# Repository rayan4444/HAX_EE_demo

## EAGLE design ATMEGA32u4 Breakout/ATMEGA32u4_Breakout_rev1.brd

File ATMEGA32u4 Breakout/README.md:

# ATMEGA32u4 Breakout v1

The ATEGA32u4 is the main microcontroller on the Arduino Leonardo and Micro. Its main advantage over the standard ATMEGA328P chip from the UNO lies in its native USB support, which makes it very easy to communicate with from a PC or SBC. This module breaks out most of the ATMEGA32u4 peripherals and is meant to be used in a Distributed Control System architecture.

## Ordering the PCB
Gerber files, Drill files and BOM for this board are provided in this repo.
If you don't know how to order PCBs, check out the HAX Wiki: [making a PCB (prototyping)](https://wiki.hax.co/Making_a_PCB_(prototyping)#Ordering_the_Board)

## Features
* Native USB
* RS-485 bus
* I2C breakout x 2
* SPI breakout x 1
* Analog pins breakout x 5 (ADC)
* PWM pins breakout x 4
* Programmable LED (on digital pin 13)
* Digital I/O breakout x 4 with optional MOSFETs:
  * solder a 0 ohm resistor where designated to use standard digital output
  * solder N-MOSFET circuitry to use it to toggle higher voltage outputs
* Optional High voltage input (for the N-MOSFET outputs)

## Programming Instructions
* The native USB port cannot be used immediately after assembling the PCB. You need to burn the Arduino Leonardo or Micro bootloader on the MCU first.
* You can use another Arduino and the SPI breakout 3x2 header to burn the bootloader ([tutorial](https://www.arduino.cc/en/tutorial/arduinoISP))
> Tip: If you have issues burning the bootloader, try connecting the receiver's (aka the new PCB) RST line to pin 10 of the programmer Arduino (aka Arduino you are using to burn the bootloader). On some boards the ICSP header's RST is not connected to pin 10 by default.

* After burning the bootloader, you can connect your ATMEGA32u4 breakout to your PCB/SBC with standard Micro USB cable and use the Arduino IDE to flash it.

## Examples
* *Short description of code in "examples" folder*
* *Link description/projects/photos where people have used this*

## Datasheets
* MCU: [ATMEGA32u4](http://ww1.microchip.com/downloads/en/devicedoc/atmel-7766-8-bit-avr-atmega16u4-32u4_datasheet.pdf)
* RS-485 transceiver: [MAX485](https://datasheets.maximintegrated.com/en/ds/MAX1487-MAX491.pdf)
* MOSFET: [IRLHM630TRPBF](https://www.infineon.com/dgdl/irlhm630pbf.pdf?fileId=5546d462533600a401535663951725a5)

## References
* [RS-485 basics](https://learn.sparkfun.com/tutorials/ast-can485-hookup-guide/introduction-to-rs485)
* Writing a custom RS485 protocol (*add link*)

## Feedback and Questions
Feel free to open an issue to report bugs, ask questions, suggest features, etc.

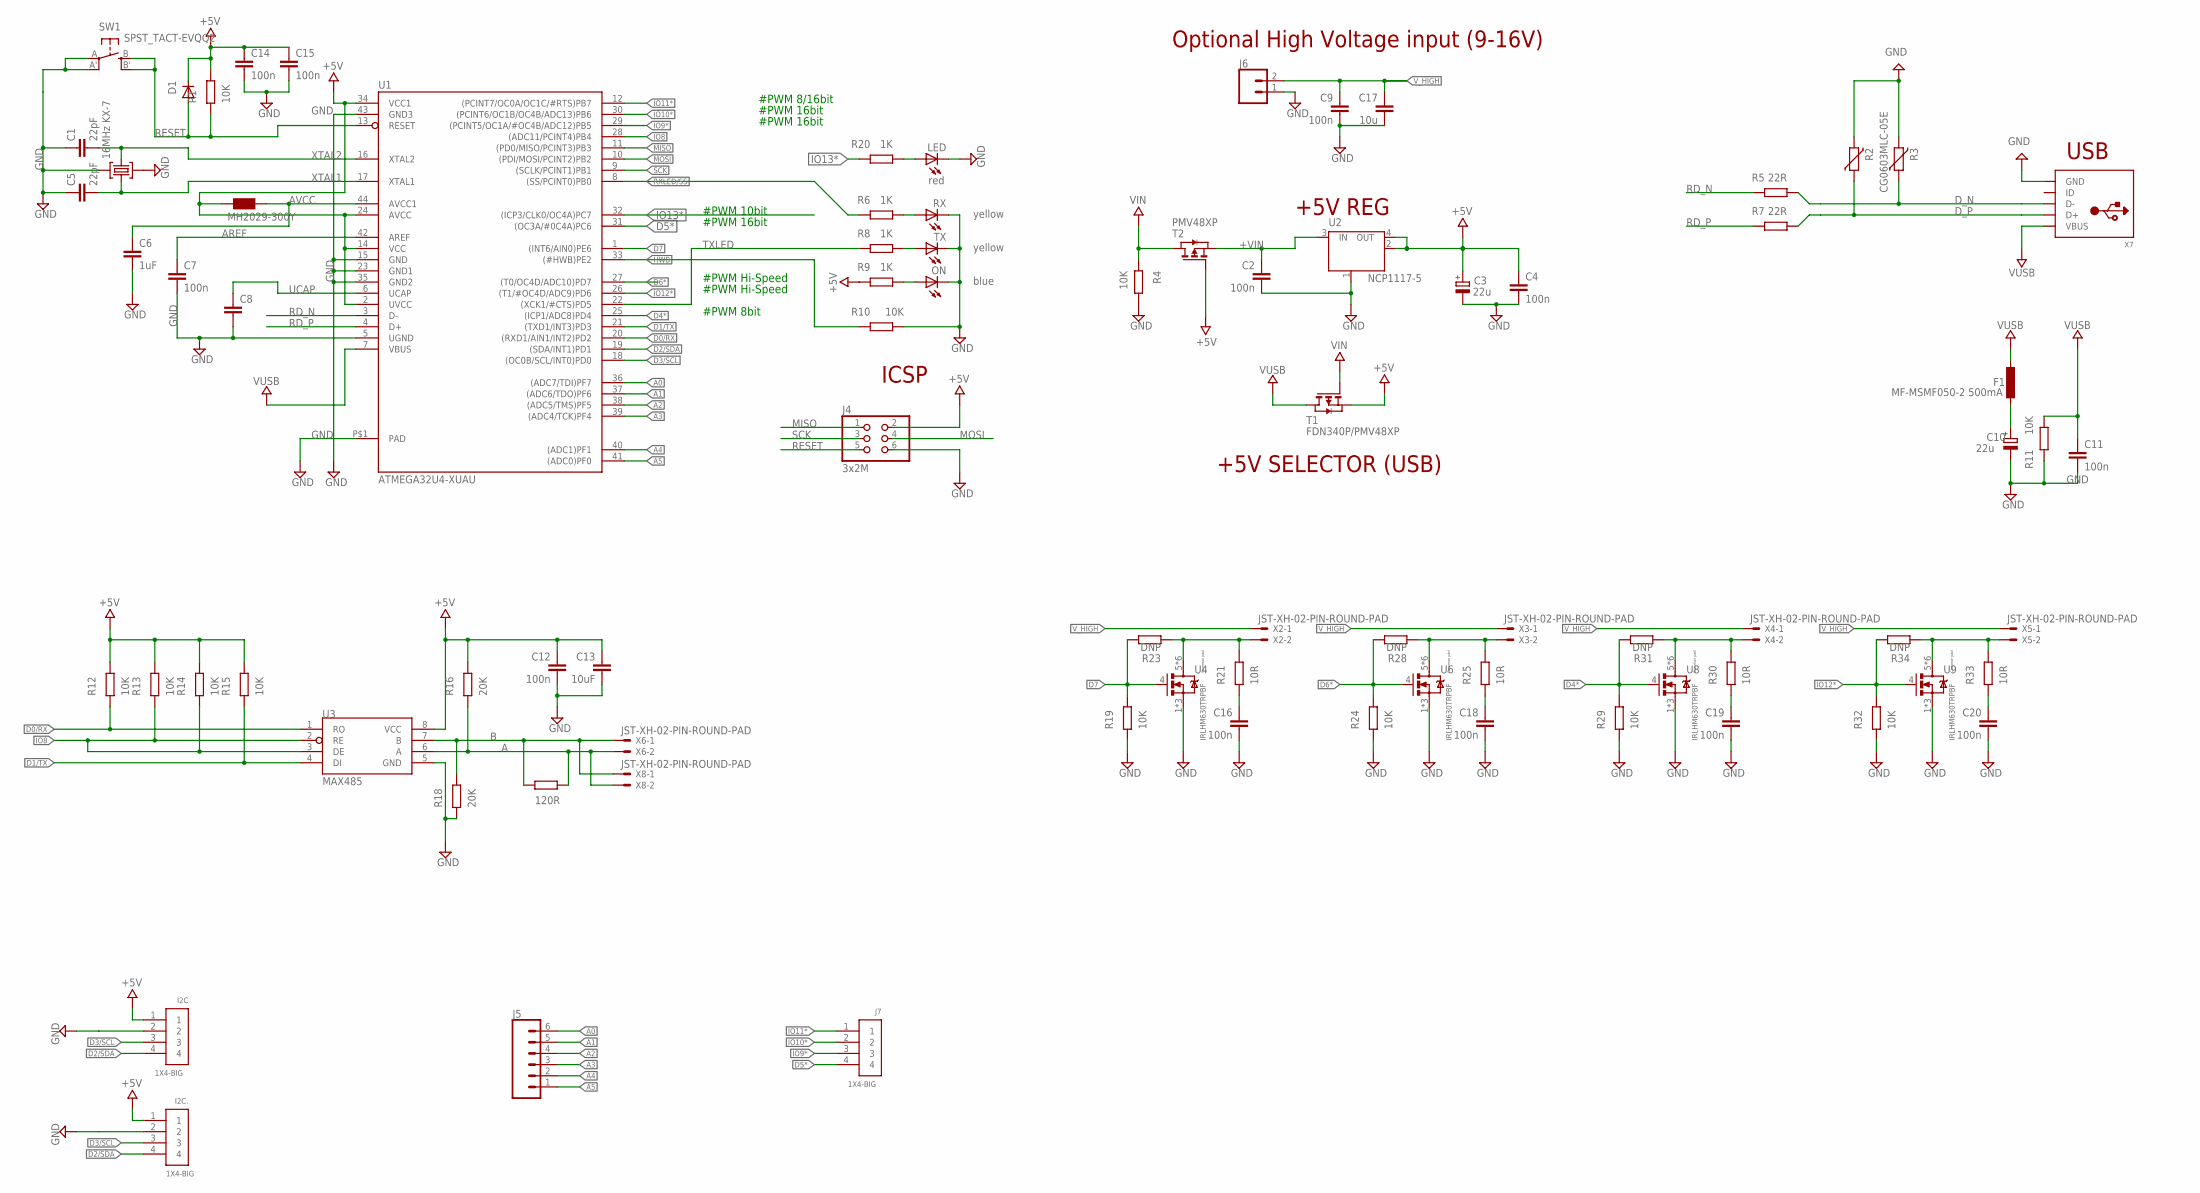
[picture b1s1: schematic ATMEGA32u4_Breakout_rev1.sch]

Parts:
C1, C5: 22pF; C0603-ROUND
C2, C4, C7, C11, C12, C14, C15, C16, C18, C19, C20: 100n; C0603-ROUND
C3, C10: 22u; SMC_B
C6, C8: 1uF; C0603-ROUND
C9: 100n; C1206
C13: 10uF; C0603-ROUND
C17: 10u; C1206
D1: CD1206-S01575; MINIMELF
F1: MF-MSMF050-2 500mA; L1812
I2C, I2C.: 1X4-BIG; 1X04-BIG
J4: 3x2M; 2X03
J5: CONN_06SILK_FEMALE_PTH; 1X06
J6: CONN_023.5MM; SCREWTERMINAL-3.5MM-2
J7: 1X4-BIG; 1X04-BIG
L2: MH2029-300Y; 0805
LED: red; CHIPLED_0805
ON: blue; CHIPLED_0805
R1, R4, R10, R11, R12, R13, R14, R15, R19, R24, R29, R32: 10K; R0603-ROUND
R2, R3: CG0603MLC-05E; CT/CN0603
R5, R7: 22R; R0603-ROUND
R6, R8, R9, R20: 1K; R0603-ROUND
R16, R18: 20K; R0603-ROUND
R17: 120R; R0603-ROUND
R21, R25, R30, R33: 10R; R0603-ROUND
R23, R28, R31, R34: DNP; R0603-ROUND
RX: yellow; CHIPLED_0805
SW1: SPST_TACT-EVQQ2; EVQ-Q2
T1: FDN340P/PMV48XP; SOT-23
T2: PMV48XP; SOT-23
TX: yellow; CHIPLED_0805
U1: ATMEGA32U4-XUAU; TQFP44-PAD
U2: NCP1117-5; SOT223
U3: MAX485; SO08
U4, U6, U8, U9: IRLHM630TRPBF
X1: 16MHz KX-7; CRYSTAL-3.2-2.5
X2, X3, X4, X5, X6, X8: JST-XH-02-PIN-ROUND-PAD; JST-XH-02-PACKAGE-ROUND-PAD
X7: MICROBUILDER_USB_MICRO_20329_V2; MICROBUILDER_4UCONN_20329_V2

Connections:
+5V: C3.+, C4.1, C12.1, C13.1, C14.1, C15.1, D1.C, I2C.1, I2C..1, J4.2, L2.1, R1.1, R9.1, R12.1, R13.1, R14.1, R15.1, R16.1, T1.2 (S), T2.3 (G), U1.2 (UVCC), U1.14 (VCC), U1.24 (AVCC), U1.34 (VCC1), U2.2 (OUT), U2.4 (OUT), U3.8 (VCC)
+VIN: C2.1, T2.2 (S), U2.3 (IN)
A: R16.2, R17.1, U3.6 (A), X6.2, X8.2
A0: J5.6, U1.36 ((ADC7/TDI)PF7)
A1: J5.5, U1.37 ((ADC6/TDO)PF6)
A2: J5.4, U1.38 ((ADC5/TMS)PF5)
A3: J5.3, U1.39 ((ADC4/TCK)PF4)
A4: J5.2, U1.40 ((ADC1)PF1)
A5: J5.1, U1.41 ((ADC0)PF0)
AREF: C7.1, U1.42 (AREF)
AVCC: C6.1, L2.2, U1.44 (AVCC1)
B: R17.2, R18.1, U3.7 (B), X6.1, X8.1
D0/RX: R12.2, U1.20 ((RXD1/AIN1/INT2)PD2), U3.1 (RO)
D1/TX: R15.2, U1.21 ((TXD1/INT3)PD3), U3.4 (DI)
D2/SDA: I2C.4, I2C..4, U1.19 ((SDA/INT1)PD1)
D3/SCL: I2C.3, I2C..3, U1.18 ((OC0B/SCL/INT0)PD0)
D4*: R29.1, R31.1, U1.25 ((ICP1/ADC8)PD4), U8.4
D5*: J7.4, U1.31 ((OC3A/#0C4A)PC6)
D6*: R24.1, R28.1, U1.27 ((T0/OC4D/ADC10)PD7), U6.4
D7: R19.1, R23.1, U1.1 ((INT6/AIN0)PE6), U4.4
D_N: R3.1, R5.2, X7.D-
D_P: R2.1, R7.2, X7.D+
GND: C1.1, C2.2, C3.-, C4.2, C5.1, C6.2, C7.2, C8.2, C9.2, C10.-, C11.2, C12.2, C13.2, C14.2, C15.2, C16.2, C17.2, C18.2, C19.2, C20.2, I2C.2, I2C..2, J4.6, J6.1, LED.C, ON.C, R2.2, R3.2, R4.1, R10.2, R11.1, R18.2, R19.2, R24.2, R29.2, R32.2, RX.C, SW1.A, SW1.A' (P1), TX.C, U1.5 (UGND), U1.15 (GND), U1.23 (GND1), U1.35 (GND2), U1.43 (GND3), U1.P$1 (PAD), U2.1 (GND/ADJ), U3.5 (GND), U4.1, U4.2 (1), U4.3 (1), U6.1, U6.2 (1), U6.3 (1), U8.1, U8.2 (1), U8.3 (1), U9.1, U9.2 (1), U9.3 (1), X1.2 (GND), X1.4 (GND), X7.BASE@1 (GND), X7.BASE@2 (GND), X7.GND, X7.SPRT@1 (GND), X7.SPRT@2 (GND), X7.SPRT@3 (GND), X7.SPRT@4 (GND)
HWB: R10.1, U1.33 ((#HWB)PE2)
IO8: R13.2, R14.2, U1.28 ((ADC11/PCINT4)PB4), U3.2 (RE), U3.3 (DE)
IO9*: J7.3, U1.29 ((PCINT5/OC1A/#OC4B/ADC12)PB5)
IO10*: J7.2, U1.30 ((PCINT6/OC1B/OC4B/ADC13)PB6)
IO11*: J7.1, U1.12 ((PCINT7/OC0A/OC1C/#RTS)PB7)
IO12*: R32.1, R34.1, U1.26 ((T1/#OC4D/ADC9)PD6), U9.4
IO13*: R20.1, U1.32 ((ICP3/CLK0/OC4A)PC7)
MISO: J4.1, U1.11 ((PD0/MISO/PCINT3)PB3)
MOSI: J4.4, U1.10 ((PDI/MOSI/PCINT2)PB2)
unnamed: R6.2, RX.A
unnamed: ON.A, R9.2
unnamed: R8.2, TX.A
unnamed: C16.1, R21.2
unnamed: LED.A, R20.2
unnamed: R21.1, R23.2, U4.5, U4.6 (5), U4.7 (5), U4.8 (5), U4.9 (5), U4.10 (5), X2.2
unnamed: C18.1, R25.2
unnamed: R25.1, R28.2, U6.5, U6.6 (5), U6.7 (5), U6.8 (5), U6.9 (5), U6.10 (5), X3.2
unnamed: C19.1, R30.2
unnamed: R30.1, R31.2, U8.5, U8.6 (5), U8.7 (5), U8.8 (5), U8.9 (5), U8.10 (5), X4.2
unnamed: C20.1, R33.2
unnamed: R33.1, R34.2, U9.5, U9.6 (5), U9.7 (5), U9.8 (5), U9.9 (5), U9.10 (5), X5.2
RD_N: R5.1, U1.3 (D-)
RD_P: R7.1, U1.4 (D+)
RESET: D1.A, J4.5, R1.2, SW1.B (S), SW1.B' (S1), U1.13 (RESET)
RXLED/SS: R6.1, U1.8 ((SS/PCINT0)PB0)
SCK: J4.3, U1.9 ((SCLK/PCINT1)PB1)
TXLED: R8.1, U1.22 ((XCK1/#CTS)PD5)
UCAP: C8.1, U1.6 (UCAP)
VIN: R4.2, T1.3 (G), T2.1 (D)
VUSB: C11.1, F1.2, R11.2, T1.1 (D), U1.7 (VBUS), X7.VBUS
VUSBD: C10.+, F1.1
V_HIGH: C9.1, C17.1, J6.2, X2.1, X3.1, X4.1, X5.1
XTAL1: C5.2, U1.17 (XTAL1), X1.3 (C2)
XTAL2: C1.2, U1.16 (XTAL2), X1.1 (C1)

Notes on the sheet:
+5V REG
ICSP
USB
+5V SELECTOR (USB)
#PWM 8bit
#PWM Hi-Speed
#PWM 16bit
#PWM 10bit
#PWM 8/16bit
Optional High Voltage input (9-16V)

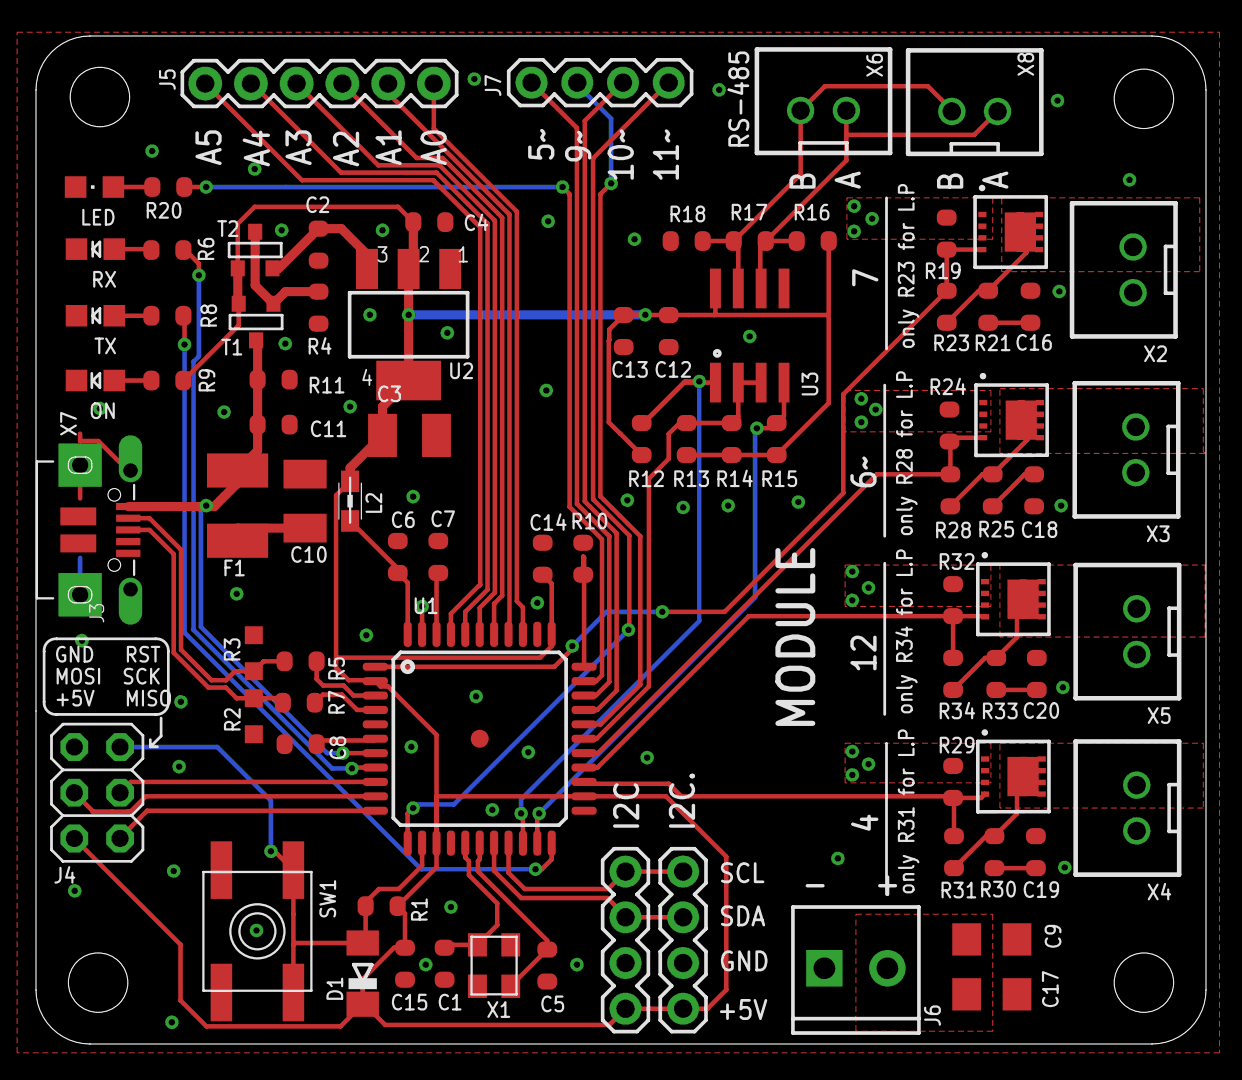
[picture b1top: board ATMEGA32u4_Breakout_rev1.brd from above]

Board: 2 copper layers, 65.0 x 56.0 mm, 82 parts (0 on the bottom side), 57 nets.

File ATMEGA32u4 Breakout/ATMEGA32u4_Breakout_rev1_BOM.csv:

ATMEGA32u4 Breakout v1 BOM,,,,,,,,,
,,,,,,,,,
#,Parts,Value,Qty,Device,Package,Description,Link,Price @1unit (RMB),Price (total)
1,"C1, C5",22pF,2,C0603,C0603,Ceramic Capacitor,Any will Do. Capacitors rated at 16V or more,0.01,0.02
2,"C2, C4, C7, C11, C12, C14, C15, C16, C18, C19, C20",100nF,11,C0603,C0603,Ceramic Capacitor,Any will Do. Capacitors rated at 16V or more,0.01,0.11
3,C9,100nF,1,C1206,C1206,Ceramic Capacitor,Any will Do. Capacitors rated at 16V or more,0.01,0.01
4,"C6, C8",1uF,2,C0603,C0603,Ceramic Capacitor,Any will Do. Capacitors rated at 16V or more,0.01,0.02
5,C13,10uF,1,C0603,C0603,Ceramic Capacitor,Any will Do. Capacitors rated at 16V or more,0.01,0.01
6,C17,10uF,1,C1206,C1206,Ceramic Capacitor,Any will Do. Capacitors rated at 16V or more,0.01,0.01
7,"C3, C10",22uF,2,C1206,C1206,Ceramic Capacitor,Any will Do. Capacitors rated at 16V or more,0.01,0.02
8,"R1, R4, R10, R11, R12, R13, R14, R15, R19, R24, R29, R32",10k,12,R0603,R0603,Resistor,Any will Do. Capacitors rated at 16V or more,0.01,0.12
9,"R21, R25, R30, R33",10R,4,R0603,R0603,Resistor,Any will Do. Capacitors rated at 16V or more,0.01,0.04
10,"R5, R7",22R,2,R0603,R0603,Resistor,Any will Do. Capacitors rated at 16V or more,0.01,0.02
11,R17,120R,1,R0603,R0603,Resistor,Any will Do. Capacitors rated at 16V or more,0.01,0.01
12,"R6, R8, R9, R20",1K,4,R0603,R0603,Resistor,Any will Do. Capacitors rated at 16V or more,0.01,0.04
13,"R16, R18",20K,2,R0603,R0603,Resistor,Any will Do. Capacitors rated at 16V or more,0.01,0.02
14,"R23, R28, R31, R34",DNP or 0R,4,R0603,R0603,Resistor,Any will Do. Capacitors rated at 16V or more,0.01,0.04
15,U1,ATMEGA32U4-XUAU,1,ATMEGA32U4-XUAU,TQFP44-PAD,,https://item.szlcsc.com/45856.html,22,22
16,D1,CD1206-S01575,1,DIODE-MINIMELF,MINIMELF,Diode,https://item.szlcsc.com/76589.html,0.18,0.18
17,"R2, R3",CG0603MLC-05E,2,VARISTORCN0603,CT/CN0603,Varistor,https://detail.tmall.com/item.htm?id=521729654981,0.3,0.6
18,"T1, T2",PMV48XP,2,PMOSSOT23,SOT-23,P channel MOSFET,https://item.szlcsc.com/76685.html,0.5,1
19,"U4, U6, U8, U9",IRLHM630TRPBF,4,IRLHM630TRPBF,IRLHM630TRPBF,N-channel MOSFET,https://item.szlcsc.com/159472.html,2.9,11.6
20,U3,MAX485,1,MAX485,SO08,RS-485 transciever,https://item.szlcsc.com/10480.html,4.63,4.63
21,F1,MF-MSMF050-2 500mA,1,F1812,F1812,PTC Resettable Fuse 500mA,https://item.szlcsc.com/17998.html,0.2,0.2
22,L2,MH2029-300Y,1,L0805,L0805,SMD EMI Suppression Ferrite Beads,https://detail.tmall.com/item.htm?id=580788207924,0.19,0.19
23,U2,NCP1117-5,1,LINEAR_MC33269ST,SOT223,Adjustable Output Low Dropout Voltage Regulator 800 mA,https://item.szlcsc.com/17999.html,1.02,1.02
24,SW1,EVQQ2,1,SPST_TACT-EVQQ2,EVQ-Q2,"SMT 6mm switch, EVQQ2 series",https://item.szlcsc.com/375651.html,0.9,0.9
25,ON,blue,1,CHIPLED0805,CHIPLED0805,LED,https://item.taobao.com/item.htm?id=534472503254,0.02,0.02
26,LED,red,1,CHIPLED0805,CHIPLED0805,LED,,0.02,0.02
27,"RX, TX",yellow,2,CHIPLED0805,CHIPLED0805,LED,,0.02,0.04
28,X1,16MHz (X322516MLB4SI),1,CRYSTAL-3.2-2.5,X322516MLB4SI,16MHz Crystal Oscillator,https://item.szlcsc.com/14393.html,0.6,0.6
29,J6,2P - 3.5MM ,1,CONN_023.5MM,SCREWTERMINAL-3.5MM-2,3.5mm 2P terminal block,https://item.taobao.com/item.htm?spm=a230r.1.14.11.63ca5f28Q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,0.2,0.2
30,X7,U254-051N-4BHJ233-S,1,USB_MICRO_20329,U254-051N-4BHJ233-S,Micro USB type B Socket,https://item.szlcsc.com/300259.html,0.3,0.3
31,"X2, X3, X4, X5, X6, X8",JST-XH-02,6,JST-XH-02,JST-XH-02,JST XH Connector 2 Pin,https://item.szlcsc.com/169360.html,0.26,1.56
Total,,,77,Total ,,,,,45.55

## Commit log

2019-09-18 Frist commit. Hardware files+README
    TODO: Upload examples, RS485 tutorial

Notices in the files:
parts and their libraries:
SparkFun-Connectors: Licensing: Creative Commons ShareAlike 4.0 International - https://creativecommons.org/licenses/by-sa/4.0
